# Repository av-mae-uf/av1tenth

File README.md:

# EML 4842: Autonomous Vehicles - 1/10th Vehicle Drivers
A repository for interfacing with the hardware onboard the AV 1/10th vehicle.

### Installation

Follow the [instructions for setup](https://av1tenth-docs.readthedocs.io/en/latest/gettingstarted/setup.html) before building this repository.

You will need to clone this repository into the ***src*** directory of a workspace. You can create the appropriate directories with:
```bash
mkdir -p ~/av1tenth_ws/src
```
***av1tenth_ws*** can be replaced with whatever name you want.

Then clone the github repository into the ***src*** directory of the workspace.
```bash
cd av1tenth_ws/src
```

```bash
git clone https://github.com/av-mae-uf/av1tenth.git
```

Build repository:

```bash
cd ~/av1tenth_ws
```

```bash
colcon build
```

Before trying to launch anything remember to source the workspace from the root directory (***~/av1tenth_ws*** in this case).
```bash
source install/setup.bash
```

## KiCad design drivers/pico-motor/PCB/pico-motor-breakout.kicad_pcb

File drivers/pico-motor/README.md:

# Pico Motor

This directory contains all files related to the Pico motor project.  
The Arduino motor carrier’s PWM has a limitation where it can only set the motor speed to two distinct values. This occurs because the Arduino’s PWM is 8-bit (0–255), while servos only use a small portion of that range (typically 7–28).  
In our case, we use the range, 14–21, where 17 represents the midpoint.

## src Directory

This directory stores the source code for the microcontroller.

- **`main.c`** – Initializes all components and runs the functions implemented in the helper files below.  
- **`crc16.h/.c`** – Implements CRC16 checksum functionality.  
- **`serial.h/.c`** – Contains UART code for communication between the microcontroller and the computer.  
- **`servo-pwm.h/.c`** – Provides generic PWM control code.  
- **`motor-control.h/.c`** – Contains application-specific motor control code that integrates the helper modules above.

## build Directory

This directory stores the compiled file `pico-motor.uf2`, which is required to upload the C code to the Pico.  
Use this directory to build the latest version of the firmware.

To build the Pico code, you must first install the Pico C SDK and build tools.

Once the toolkit is installed, cd to the `build` directory and run:

```bash
cmake ..
make
```

## PCB Directory

This directory contains the KiCad project files for the Pico Motor breakout board.

If you need to order more boards, use the production-ready ZIP file located at: `PCB/production/pico-motor-breakout.zip`

You can upload this file directly to JLCPCB to manufacture new boards.

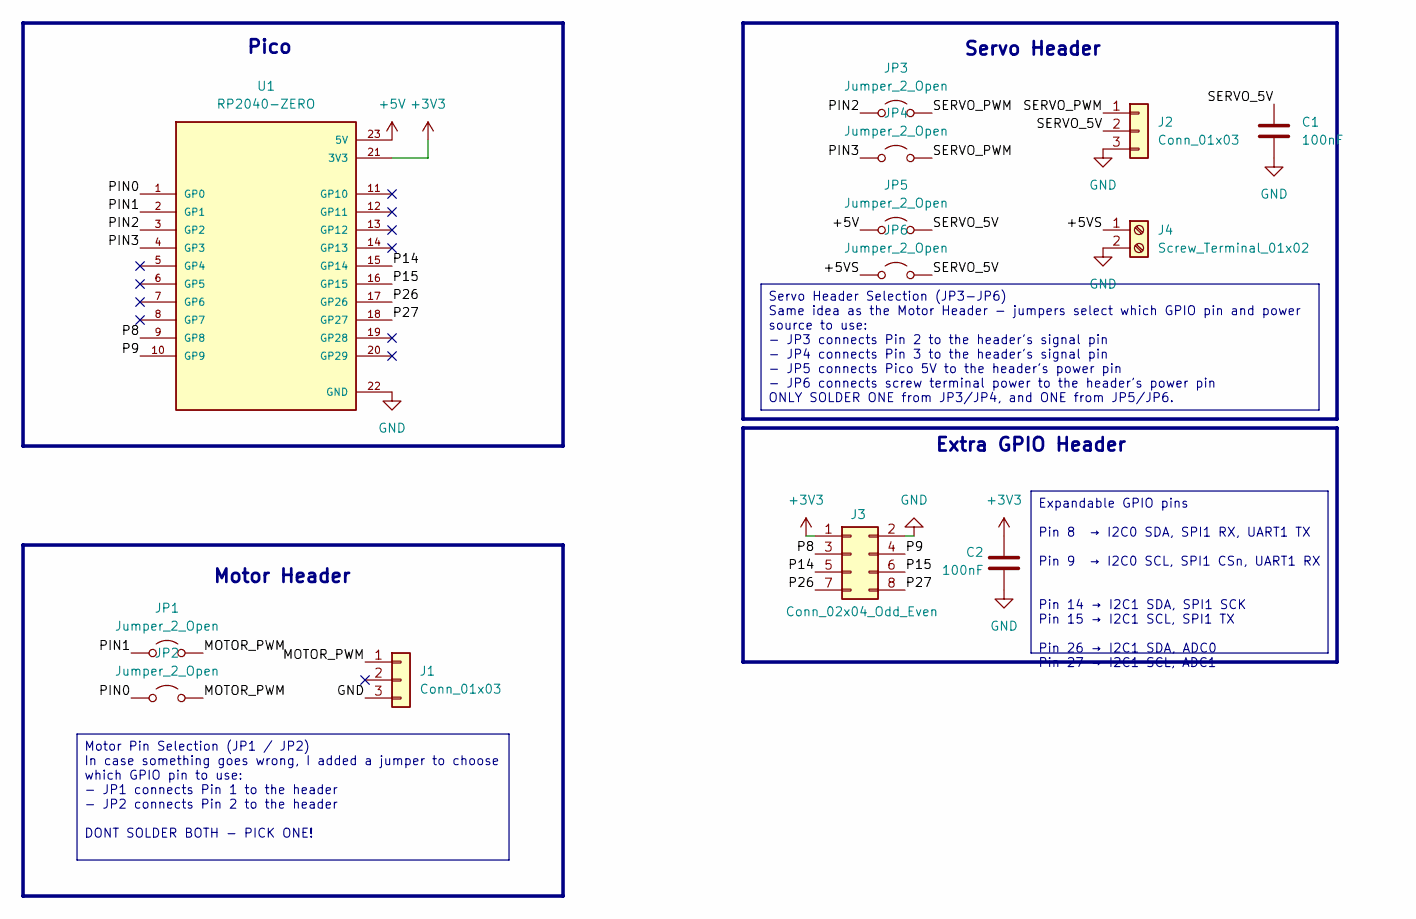
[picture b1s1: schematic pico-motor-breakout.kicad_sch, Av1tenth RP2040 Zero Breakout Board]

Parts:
C1, C2: 100nF; C_0603_1608Metric
J1, J2: Conn_01x03; PinHeader_1x03_P2.54mm_Vertical
J3: Conn_02x04_Odd_Even; PinHeader_2x04_P2.54mm_Vertical
J4: Screw_Terminal_01x02; TerminalBlock_Xinya_XY308-2.54-2P_1x02_P2.54mm_Horizontal
JP1, JP2, JP3, JP4, JP5, JP6: Jumper_2_Open; SolderJumper-2_P1.3mm_Open_TrianglePad1.0x1.5mm
U1: RP2040-ZERO; MODULE_RP2040-ZERO; PARTREV NA

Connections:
+3V3: C2.1, J3.1, U1.21 (3V3)
+5V: JP5.1 (A), U1.23 (5V)
/+5VS: J4.1, JP6.1 (A)
/MOTOR_PWM: J1.1, JP1.2 (B), JP2.2 (B)
/P8: J3.3, U1.9 (GP8)
/P9: J3.4, U1.10 (GP9)
/P14: J3.5, U1.15 (GP14)
/P15: J3.6, U1.16 (GP15)
/P26: J3.7, U1.17 (GP26)
/P27: J3.8, U1.18 (GP27)
/PIN0: JP2.1 (A), U1.1 (GP0)
/PIN1: JP1.1 (A), U1.2 (GP1)
/PIN2: JP3.1 (A), U1.3 (GP2)
/PIN3: JP4.1 (A), U1.4 (GP3)
/SERVO_5V: C1.1, J2.2, JP5.2 (B), JP6.2 (B)
/SERVO_PWM: J2.1, JP3.2 (B), JP4.2 (B)
GND: C1.2, C2.2, J1.3, J2.3, J3.2, J4.2, U1.22 (GND)

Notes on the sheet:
Servo Header
Pico
Extra GPIO Header
Motor Header
Motor Pin Selection (JP1 / JP2) In case something goes wrong, I added a jumper to choose which GPIO pin to use: - JP1 connects Pin 1 to the header - JP2 connects Pin 2 to the header DONT SOLDER BOTH - PICK ONE!
Servo Header Selection (JP3-JP6) Same idea as the Motor Header - jumpers select which GPIO pin and power source to use: - JP3 connects Pin 2 to the header's signal pin - JP4 connects Pin 3 to the header's signal pin - JP5 connects Pico 5V to the header's power pin - JP6 connects screw terminal powe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
Expandable GPIO pins Pin 8 → I2C0 SDA, SPI1 RX, UART1 TX Pin 9 → I2C0 SCL, SPI1 CSn, UART1 RX Pin 14 → I2C1 SDA, SPI1 SCK Pin 15 → I2C1 SCL, SPI1 TX Pin 26 → I2C1 SDA, ADC0 Pin 27 → I2C1 SCL, ADC1

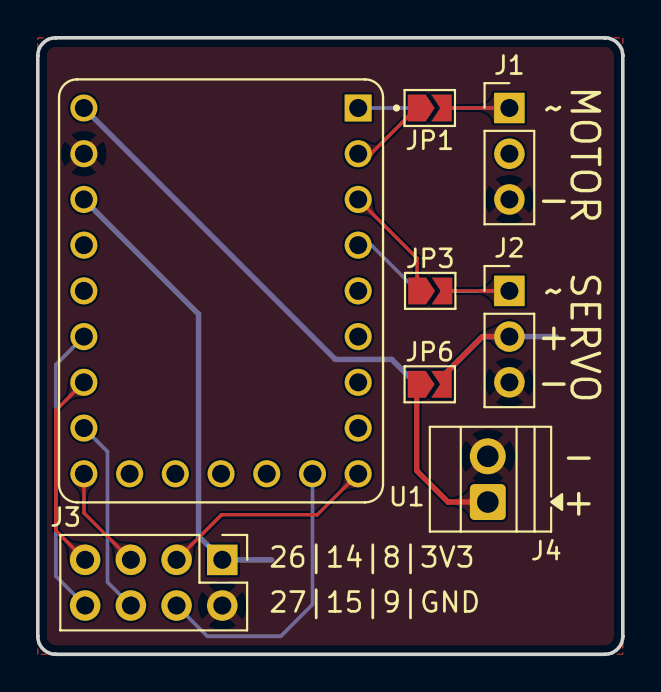
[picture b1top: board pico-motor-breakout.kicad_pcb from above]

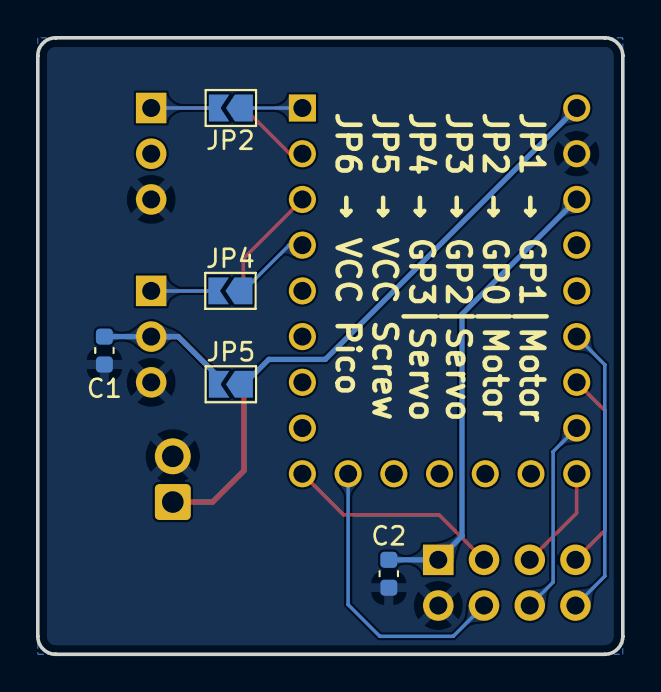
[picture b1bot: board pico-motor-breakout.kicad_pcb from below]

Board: 2 copper layers, 32.5 x 34.2 mm, 13 parts (5 on the bottom side), 17 nets.

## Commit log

2022-08-24 Second Commit
2022-08-25 Added Ports for pololu
2022-09-08 forcing float
2022-09-21 Adding bag file
2022-09-21 capping linear speed
2022-09-23 Adding steer offset and ports automation
2022-09-23 Capping linear speed.
2022-09-23 Adding twist file to source as a demo
2022-09-23 adding correct user to ports.py
2022-09-23 Updating motor driver
2022-09-25 Adding rviz launch file
2022-09-26 Refactoring a bunch of code
2022-09-27 fixing data outputs of odometry
2022-09-28 Adding some additional changes and completing refactoring
2022-09-28 Refactor (#1)
    * Refactoring a bunch of code
    * fixing data outputs of odometry
    * Adding some additional changes and completing refactoring
2022-10-04 Refactoring, and adding comments to message files
2022-10-04 Adding rviz config file to lidar_launch
2022-10-11 Adding z_offset parameter
2022-10-18 Update ports.py
    Changed file name to 00386325 for 'cimar' car.
2022-10-18 Fixed errors with gps package breaking, and odom data issues
2022-10-18 Changing Baud rates
2022-10-18 Adding serial_in_waiting() for encoder reads
2022-10-19 Changing message for gps to PoseStamped. Removing old gps driver
2022-10-19 Adding posestamped to gps driver
2022-10-19 adding message info
2022-10-21 Adding dependencies to package.xml's
2022-10-21 Changing run_depend to exec_depend
2022-10-21 Adding variable call to prevent refrenced before assignment error
2022-10-21 Fixing Pose message
2022-10-24 changing gps port
2022-10-28 Adding Bag Files
2022-11-16 modifying message to have velocity and error to compare controllers
2022-11-22 Added code to remove unneccesary serial writes.
2022-11-22 Fixed isclose error
2022-11-22 Error string hack
2022-11-22 string fix
2022-11-22 debugging
2022-11-22 debugging null character
2022-11-22 fixed isopen
2022-11-22 semi final commit, awaitng testing.
2022-11-24 Patrick branch (#5)
    * Added code to remove unneccesary serial writes.
    * Fixed isclose error
    * Error string hack
    * string fix
    * debugging
    * debugging null character
2022-11-24 experimental update
2022-12-16 Updating GPS to publish Nav Sat Fix. Updating package name for neo6m_driver. removing test_depend from packages
2022-12-17 Adding Co-variances for gps driver
2023-02-03 Added arduino code for motor carrier
2023-02-06 WIP commit
2023-02-12 Updating driver names, changing actuator message to ackermann structure, adding vehicle launch package
2023-02-12 Updating callback names
2023-02-13 Drivers branch (#7)
    * experimental update
    * Updating GPS to publish Nav Sat Fix. Updating package name for neo6m_driver. removing test_depend from packages
    * Adding Co-variances for gps driver
    * Updating driver names, changing actuator message to ackermann structure, adding vehicle launch package
    * Updating callback names
    ---------
2023-02-16 Fixed bug on shutdown for pololu_driver.
2023-02-16 Incremental changes
2023-02-22 Fixing launch files
2023-03-15 Updated arduino motor carrier code
2023-03-20 creating motor_carrier_driver
2023-03-20 Arduino update and driver update
2023-03-23 Updating Driver code, removing odometry driver and updating launch files
2023-03-23 Adding button inputs for leds
2023-03-23 fixing issues
2023-03-23 led reset state
2023-03-23 Changing heartbeat timeout
2023-03-23 Adding init state value
2023-03-23 adding safe state
2023-03-23 correcting object
2023-04-03 motor_carrier branch update
2023-04-03 Motor carrier (#8)
    * Added arduino code for motor carrier
    * WIP commit
    * Incremental changes
    * Updated arduino motor carrier code
    * creating motor_carrier_driver
    * Arduino update and driver update
2023-04-04 fixing axes
2023-04-05 fixing motor_carrier_serial driver, removing twist.angular, adding callback groups
2023-04-05 removing node from executor.spin
2023-04-10 logging encoder counts
2023-04-21 Adding time stamp to odometry and frame_id Commenting out encoder wheel counts
2023-04-24 Changing limiter settings
2023-09-07 Clean up and slight Arduino code modification
2023-09-07 formatting
2023-09-09 Cleanup
2023-09-18 Cleanup and revert some previous Arduino code changes.
2023-10-04 fixing limiter math
2025-08-07 Considering adding a tiny RP2040 to do motor control, the current motor carrier doesnt have fine PWM control and it seems extremely hard to flash new firmware onto it
2025-08-07 Started writing functions needed for pico to read messages from computer and change angles TODO: - put protoypes into seperate .h files and functions in .c files - write code that reads from UART(Ser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
2025-08-07 Split the code into h and c files, and tested setAngle function. TODO: - write code that reads from UART(Serial) and uses message to update servo - Test CRC16 function, not sure if I used the write i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
2025-08-08 Started Writing Code that Can communicate with USB UART (SERIAL). Still needs to be tested.
2025-08-08 Tried testing CRC 16 CCITT, both python and C give me the (allegedly) wrong values. Need to look into this.
2025-08-08 Fiogured out that the CRC needed what XMODEM not CCITT. CCITT was a misappropriation in the python CRC library. The cars use an older version of the library which still uses the name CCITT, if update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
2025-08-09 Tested serial functions, appears to be able to detrmine the correct CRC value
2025-08-12 Minor touhing up the C code, Wrote Python Test serial script - Removed from TODOs - Changed some of the formating of a few functions and placement of some variables - wrote script that connects to pi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
2025-08-15 Updated CRC to have different configurations
2025-08-15 Updated Serial Test Script to look for Pico Port more dynamically.
    TODO: maybe look into other options, not much of a fan of this method
2025-08-15 Updated Motor Carrier Driver to write to pico
2025-08-22 Intergrating onto the Car, changed PWM range to be closer to Arduino.
2025-08-22 Found out there is a custom udev rule for arduino, gps, and lidar. Added pico to it
2025-08-22 Updated motor carrier driver to use Pico Udev rule location
2025-10-10 Update 99-sensor.rules
    Didnt notice duplicate line
2025-10-10 Added uf2 file
2025-10-13 Added PCB files and Pico Motor README
